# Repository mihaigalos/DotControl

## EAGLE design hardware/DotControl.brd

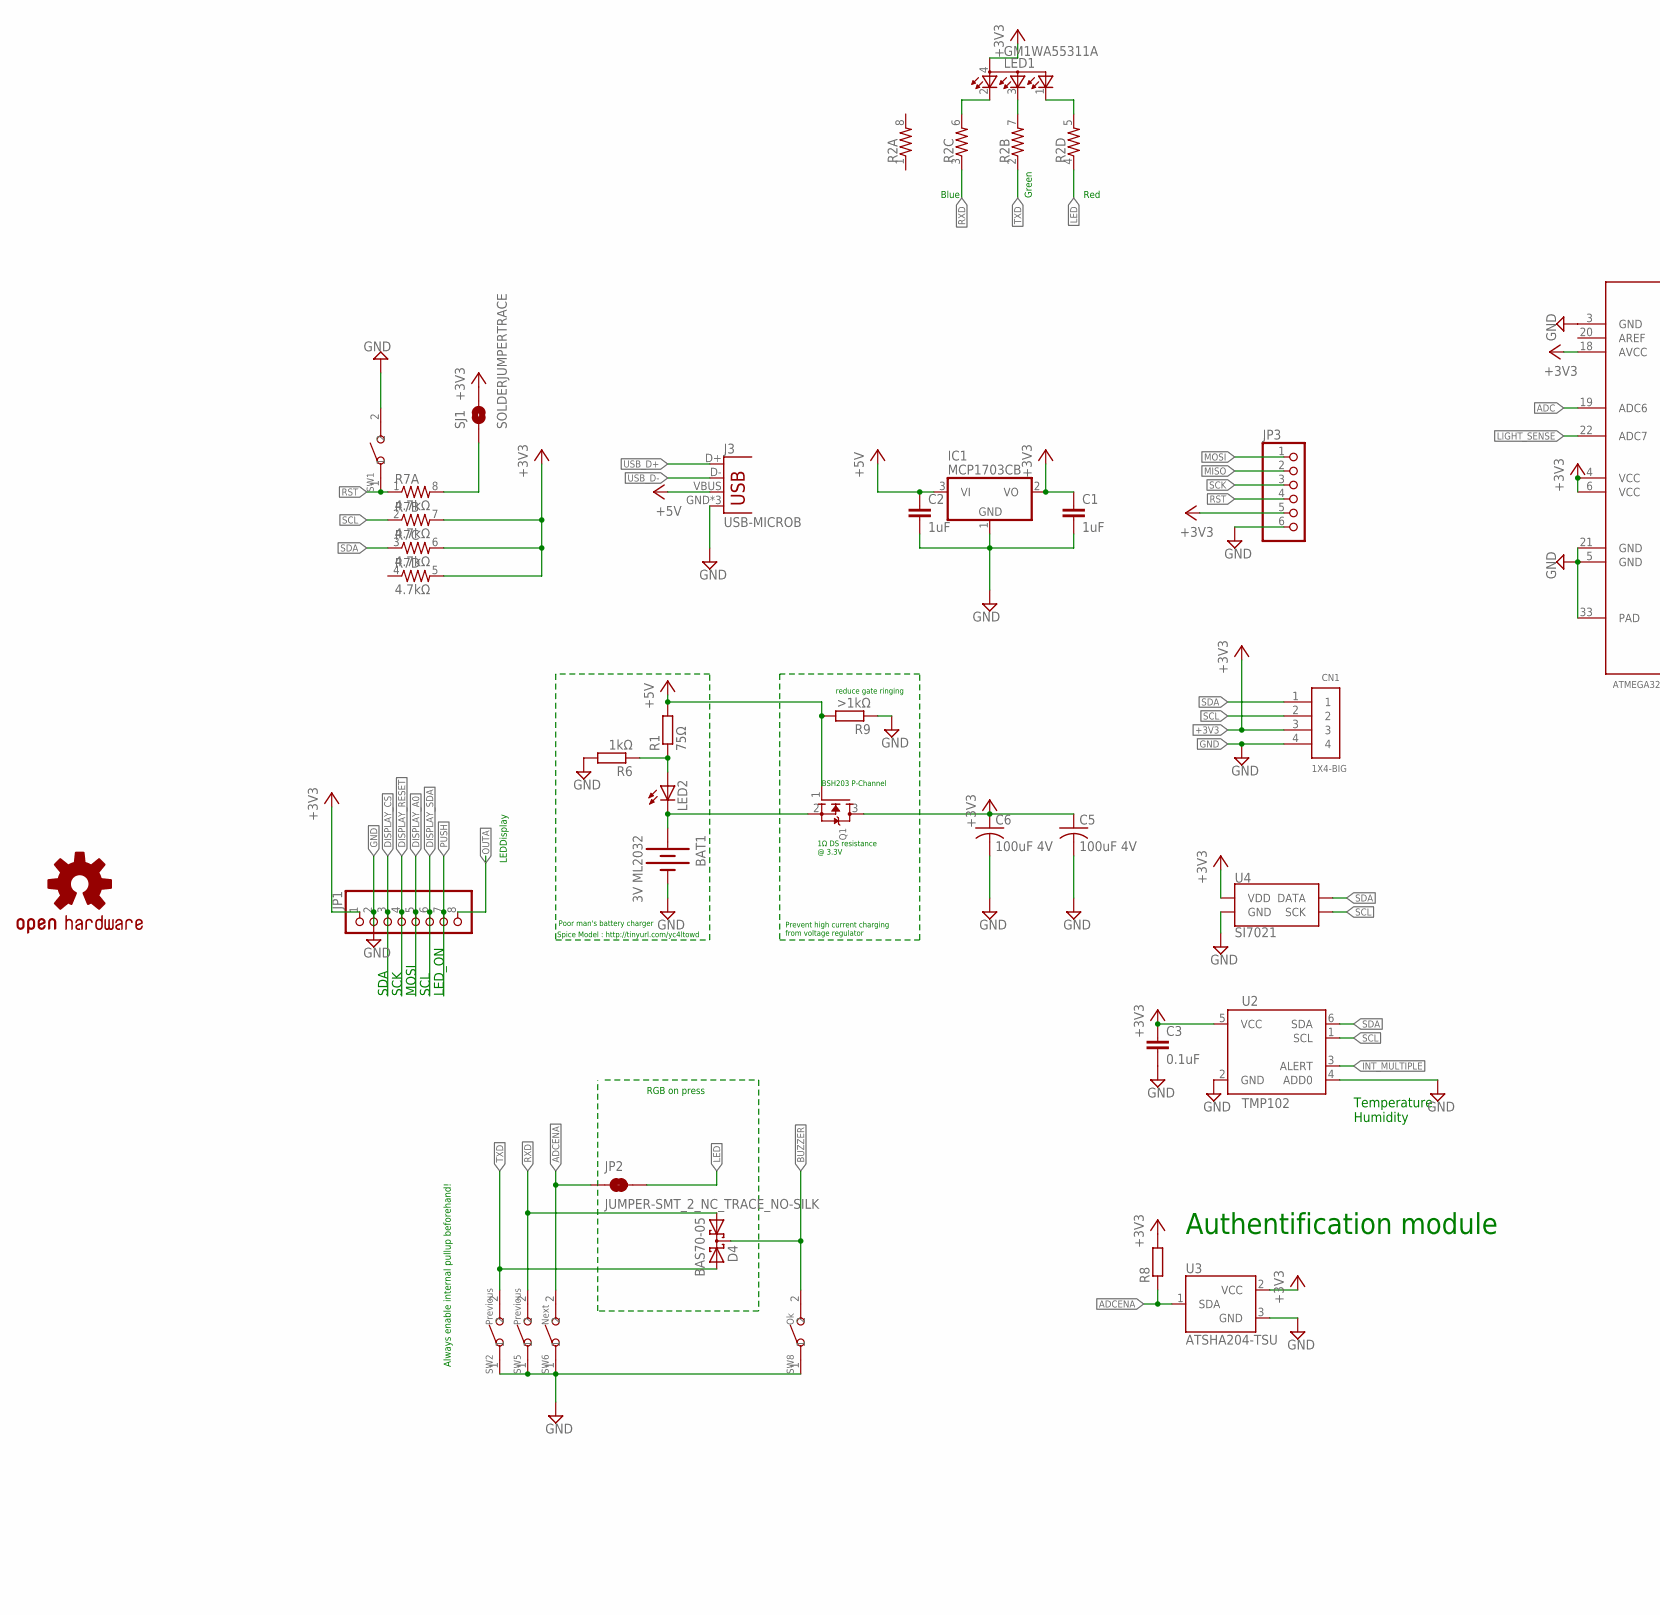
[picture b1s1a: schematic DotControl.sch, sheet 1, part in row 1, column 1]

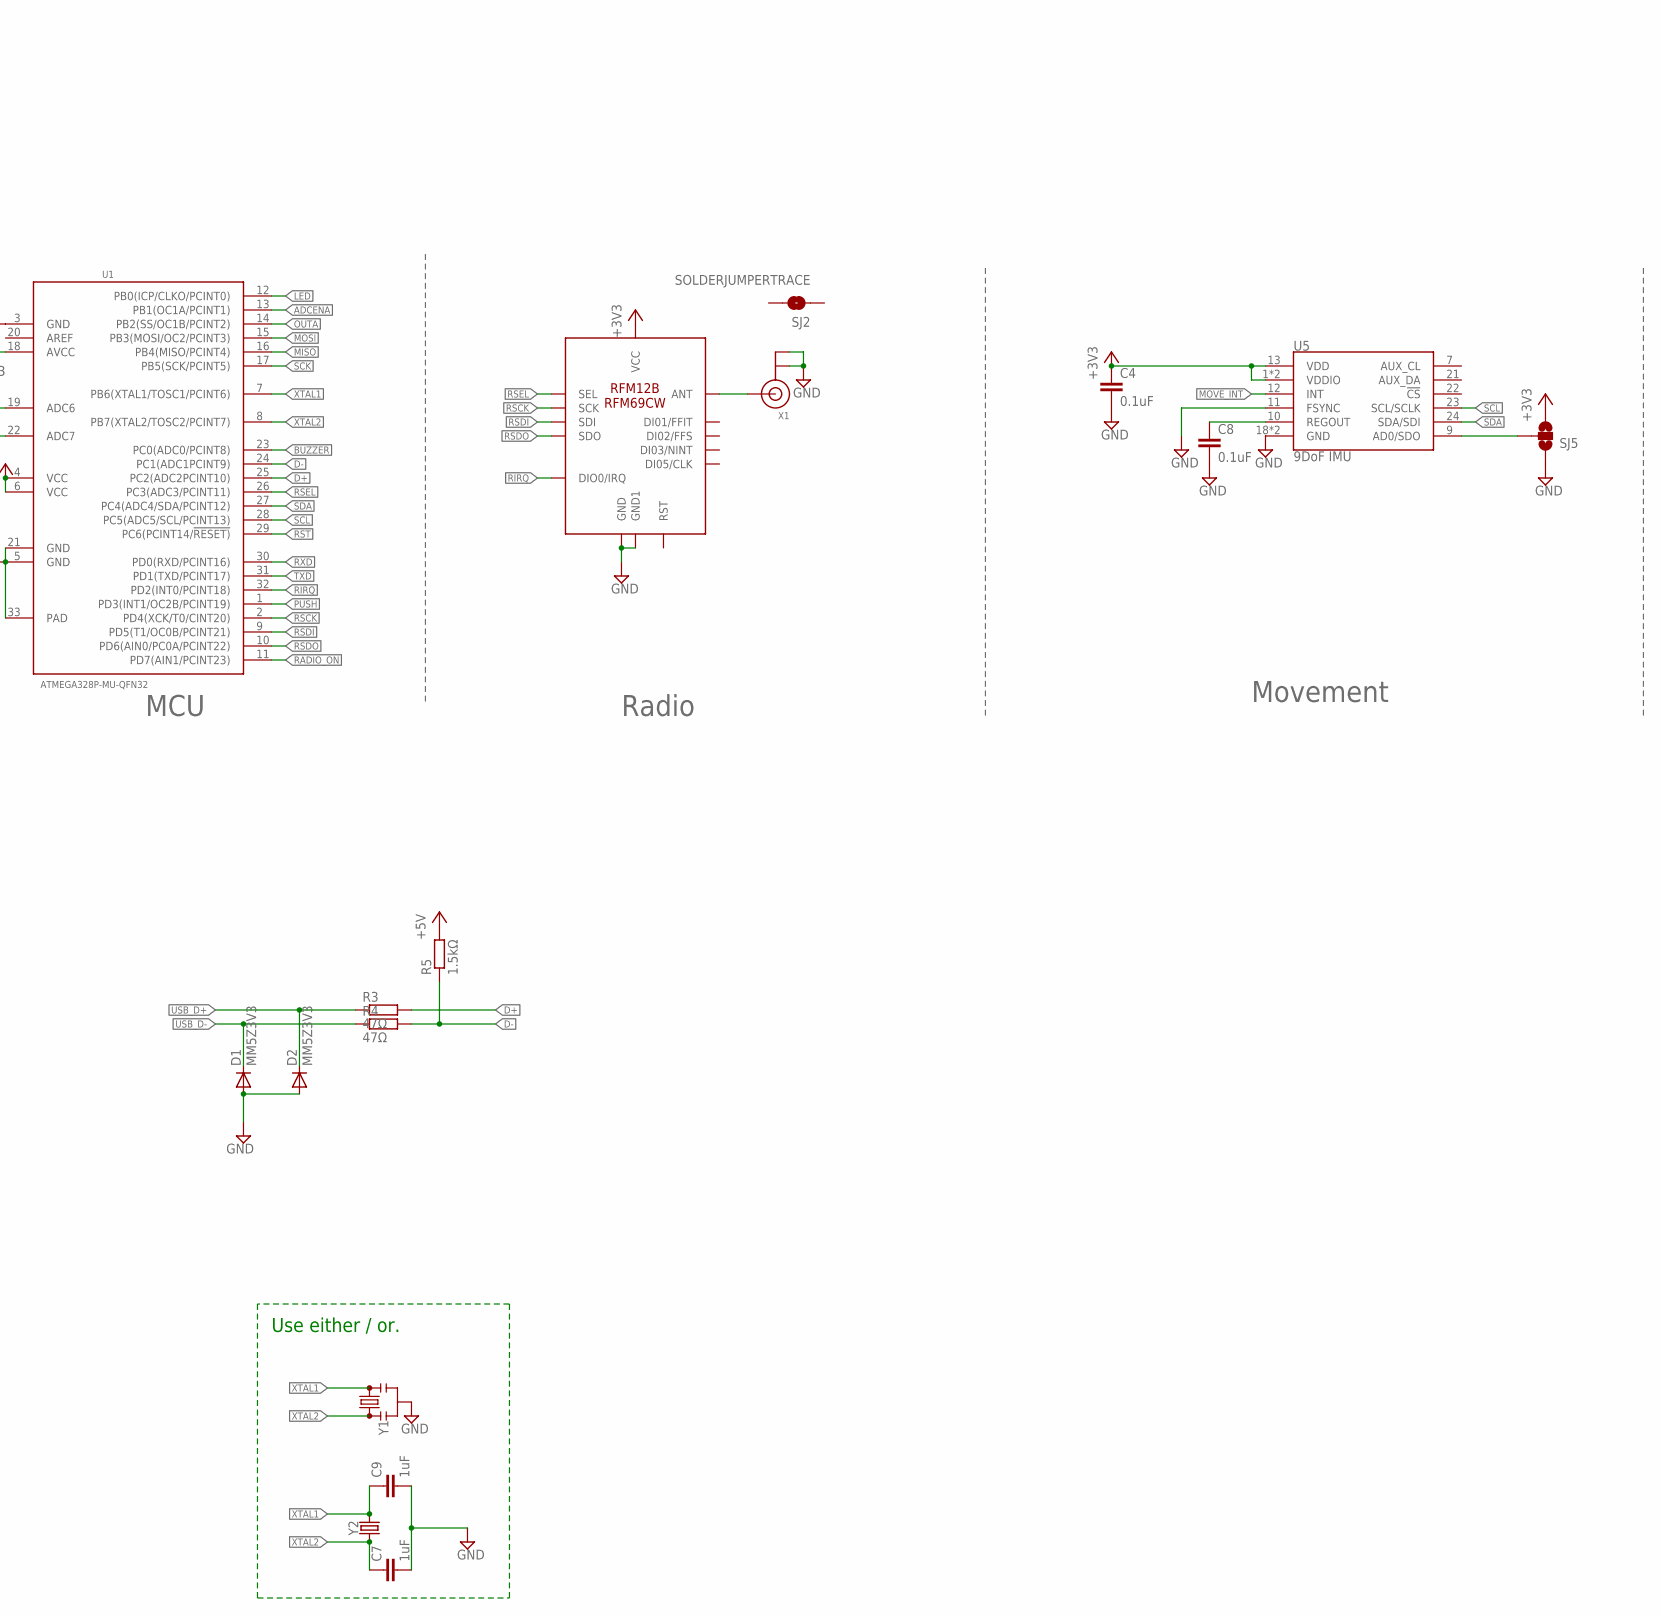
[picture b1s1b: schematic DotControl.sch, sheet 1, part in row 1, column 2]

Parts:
BAT1: 3V ML2032; BATTCOM_20MM_PTH
C1, C2, C7, C9: 1uF; C0603
C3, C4, C8: 0.1uF; C0603
C5, C6: 100uF 4V; C3216
CN1: 1X4-BIG; 1X04-BIG
D1, D2: MM5Z3V3; SOD523
D4: BAS70-05; SOT23
IC1: MCP1703CB; SOT23
J3: USB-MICROB
JP1: PINHD-1X8CLEANBIG; 1X08-CLEANBIG
JP2: JUMPER-SMT_2_NC_TRACE_NO-SILK; SMT-JUMPER_2_NC_TRACE_NO-SILK
JP3: PINHD-1X6; 1X06
LED1: GM1WA55311A
LED2: LED0603; LED-0603
Q1: MOSFET-NREFLOW; SOT23
R1: 75Ω; R0603
R2: RESISTOR-ARRAY0603-ARV; 0603-ARV
R3, R4: 47Ω; R0603
R5: 1.5kΩ; R0603
R6: 1kΩ; R0603
R7: 4.7kΩ; 0603-ARV
R8: R-EU_R0603; R0603
R9: >1kΩ; R0603
SJ1, SJ2: SOLDERJUMPERTRACE; SJ_2S-TRACE
SJ5: SOLDERJUMPER_2WAYS; SJ_3
SW1: SMD-BUTTON(2P-6.0X3.0X2.5MM)-DHT-1163S; SW2-4.0-6.0X3.0X2.5MM
SW2, SW5: Previous; SW2-4.0-6.0X3.0X2.5MM
SW6: Next; SW2-4.0-6.0X3.0X2.5MM
SW8: Ok; SW2-4.0-6.0X3.0X2.5MM
U1: ATMEGA328P-MU-QFN32; QFN32G-0.5-5X5MM
U2: TMP102; SOT563
U3: ATSHA204-TSU; SOT23-3
U4: SI7021; DFN-6-3X3-SI7021
U5: 9DoF IMU; QFN24-3X3
U$1: RFM12B/69CW
U$2: OSHW-LOGOL; OSHW-LOGO-L
X1: ANTENNA_U.FL; U.FL
Y1: RESONATORSMD-3.2X1.3; RESONATOR-SMD-3.2X1.3
Y2: CRYSTALSMD-3.2X1.5; CRYSTAL-SMD-3.2X1.5MM

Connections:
+3V3: C1.1, C3.1, C4.1, C5.1, C6.1, CN1.3, IC1.2 (VO), JP1.1, JP3.5, LED1.4 (A), Q1.3 (D), R7.5 (2), R7.6 (2), R7.7 (2), R8.2, SJ1.2, SJ5.3, U1.4 (VCC), U1.6 (VCC), U1.18 (AVCC), U2.5 (VCC), U3.2 (VCC), U4.VDD, U5.1 (VDDIO), U5.8 (VDDIO), U5.13 (VDD), U$1.VDD (VCC)
+5V: C2.1, IC1.3 (VI), J3.VBUS, Q1.1 (G), R1.2, R5.2, R9.2
ADC: U1.19 (ADC6)
ADCENA: JP2.1, R8.1, SW6.2, U1.13 (PB1(OC1A/PCINT1)), U3.1 (SDA)
BLUE: LED1.2 (CRED), R2.6 (2)
BUZZER: D4.3 (C), SW8.2, U1.23 (PC0(ADC0/PCINT8))
D+: R3.2, U1.25 (PC2(ADC2PCINT10))
D-: R4.2, R5.1, U1.24 (PC1(ADC1PCINT9))
DISPLAY_A0: JP1.5
DISPLAY_CS: JP1.3
DISPLAY_RESET: JP1.4
DISPLAY_SDA: JP1.6
GND: BAT1.2 (-), C1.2, C2.2, C3.2, C4.2, C5.2, C6.2, C7.2, C8.2, C9.2, CN1.4, D1.A, D2.A, IC1.1 (GND), J3.GND, J3.MT1 (GND), J3.MT2 (GND), JP1.2, JP3.6, R6.2, R9.1, SJ5.1, SW1.2, SW2.1, SW5.1, SW6.1, SW8.1, U1.3 (GND), U1.5 (GND), U1.21 (GND), U1.33 (PAD), U2.2 (GND), U2.4 (ADD0), U3.3 (GND), U4.GND, U5.11 (FSYNC), U5.18 (GND), U5.20 (GND), U$1.GND, U$1.GND1, X1.1 (GND), X1.2 (GND), Y1.2
GREEN: LED1.3 (CBLUE), R2.7 (2)
INT_MULTIPLE: U2.3 (ALERT)
LED: JP2.2, R2.4 (1), U1.12 (PB0(ICP/CLKO/PCINT0))
LIGHT_SENSE: U1.22 (ADC7)
MISO: JP3.2, U1.16 (PB4(MISO/PCINT4))
MOSI: JP3.1, U1.15 (PB3(MOSI/OC2/PCINT3))
MOVE_INT: U5.12 (INT)
unnamed: LED2.A, R1.1, R6.1
unnamed: R7.8 (2), SJ1.1
unnamed: U$1.ANT, X1.3 (SIGNAL)
unnamed: SJ5.2, U5.9 (AD0/SDO)
unnamed: C8.1, U5.10 (REGOUT)
unnamed: BAT1.1 (+), LED2.C, Q1.2 (S)
OUTA: JP1.8, U1.14 (PB2(SS/OC1B/PCINT2))
PUSH: JP1.7, U1.1 (PD3(INT1/OC2B/PCINT19))
RADIO_ON: U1.11 (PD7(AIN1/PCINT23))
RED: LED1.1 (CGREEN), R2.5 (2)
RIRQ: U1.32 (PD2(INT0/PCINT18)), U$1.IRQ (DIO0/IRQ)
RSCK: U1.2 (PD4(XCK/T0/CINT20)), U$1.SCK
RSDI: U1.9 (PD5(T1/OC0B/PCINT21)), U$1.SDI
RSDO: U1.10 (PD6(AIN0/PC0A/PCINT22)), U$1.SDO
RSEL: U1.26 (PC3(ADC3/PCINT11)), U$1.SEL
RST: JP3.4, R7.1, SW1.1, U1.29 (PC6(PCINT14/!RESET))
RXD: D4.1 (A1), R2.3 (1), SW5.2, U1.30 (PD0(RXD/PCINT16))
SCK: JP3.3, U1.17 (PB5(SCK/PCINT5))
SCL: CN1.2, R7.2 (1), U1.28 (PC5(ADC5/SCL/PCINT13)), U2.1 (SCL), U4.SCK, U5.23 (SCL/SCLK)
SDA: CN1.1, R7.3 (1), U1.27 (PC4(ADC4/SDA/PCINT12)), U2.6 (SDA), U4.DATA, U5.24 (SDA/SDI)
TXD: D4.2 (A2), R2.2 (1), SW2.2, U1.31 (PD1(TXD/PCINT17))
USB_D+: D2.C, J3.D+, R3.1
USB_D-: D1.C, J3.D-, R4.1
XTAL1: C9.1, U1.7 (PB6(XTAL1/TOSC1/PCINT6)), Y1.3, Y2.P$2 (2)
XTAL2: C7.1, U1.8 (PB7(XTAL2/TOSC2/PCINT7)), Y1.1, Y2.P$1 (1)

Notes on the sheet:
MCU
Radio
Blue
Green
Red
Always enable internal pullup beforehand!
Temperature Humidity
MOSI
SCK
SDA
SCL
LED_ON
LEDDisplay
Authentification module
RGB on press
Movement
Spice Model : http://tinyurl.com/yc4ltowd
BSH203 P-Channel
Poor man's battery charger
Prevent high current charging from voltage regulator
reduce gate ringing
1Ω DS resistance @ 3.3V
Use either / or.

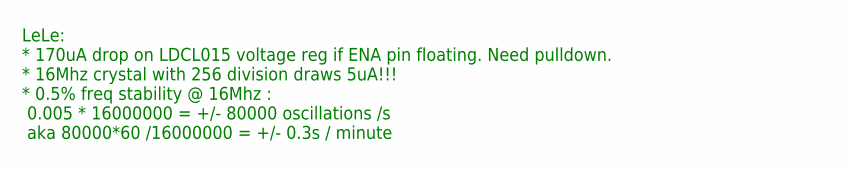
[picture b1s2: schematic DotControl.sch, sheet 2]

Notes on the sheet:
LeLe: * 170uA drop on LDCL015 voltage reg if ENA pin floating. Need pulldown. * 16Mhz crystal with 256 division draws 5uA!!! * 0.5% freq stability @ 16Mhz : 0.005 * 16000000 = +/- 80000 oscillations /s aka 80000*60 /16000000 = +/- 0.3s / minute

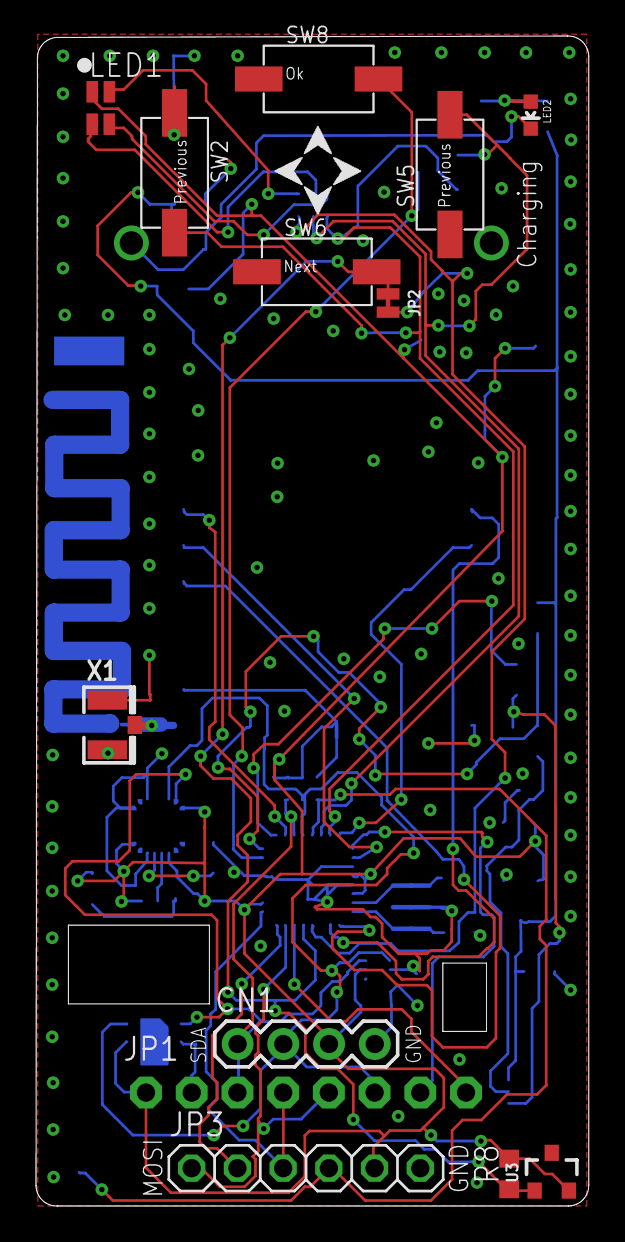
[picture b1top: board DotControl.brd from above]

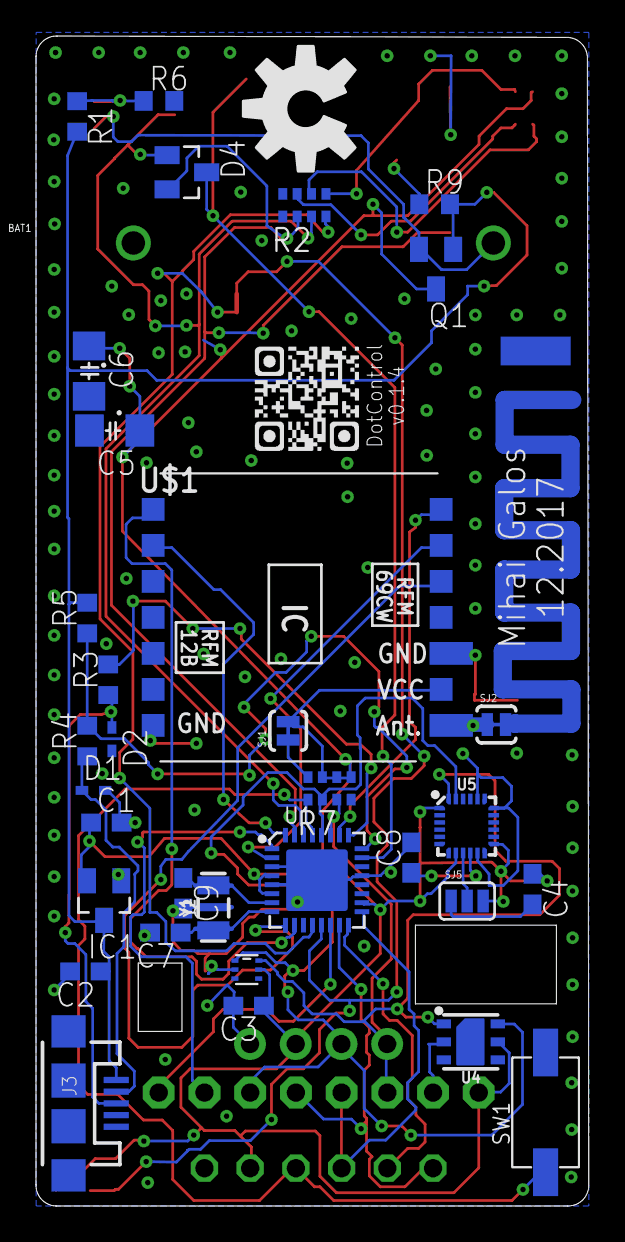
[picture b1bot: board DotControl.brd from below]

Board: 2 copper layers, 30.7 x 65.0 mm, 49 parts (36 on the bottom side), 36 nets.

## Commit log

2017-10-31 Initial version
2017-10-31 Add RGB and crystal
2017-10-31 Add strong GND plane
2017-10-31 Checkpoint
2017-10-31 Add charging led
2017-10-31 Add TMP112 temperature sensor
2017-11-02 Solidify GND plane
2017-11-02 Add connections for 128x128
2017-11-02 Add hardware/ and .gitignore
2017-11-02 Update ignore rules
2017-11-02 Add QR and timestamp
2017-11-03 Update QR rotation
2017-11-03 Update display supply to 3.3V, charging of battery
2017-11-03 Rotate temp sensor
2017-11-03 Minor rearrange wires
2017-11-03 Improve routing and vias
2017-11-03 Add rounded corners
2017-11-05 Amend
2017-11-05 Add CryptoAuthentication module
2017-11-05 Reposition crypto module
2017-11-18 Add key to RGB
2017-11-18 Add PCB antenna
2017-11-18 Increase clearance of antenna
2017-11-18 Add missing 3V3 connection to battery
2017-11-18 Improve GND
2017-11-18 Edit ToDos
2017-11-19 Add HW support for USB bootloading
2017-11-19 Reassign push buttons
2017-11-19 Setting vias near rgb R-array further apart
2017-11-19 Swap R with B @ pushbutton
2017-11-19 Light RGB composite colors on push press
2017-11-19 Add Si7021 temp sensor
2017-11-19 Add I2C text
2017-11-20 [Beta] Add HW support for MPU9250
2017-11-22 Add caps for MPU9250, V divider for battery charge
2017-11-22 Tidy up logos of Rs
2017-11-22 Readjust R values for charger, add Spice link
2017-11-25 Add pulldown on ENA pin of voltage reg to prefent 150uA quiescent current
2017-11-25 Add pulldown on ENA pin of voltage reg to prevent 150uA quiescent current
2017-11-25 [Intermediate] Improve coincell charging
2017-11-26 Replace LDO with low quiescence regulator
2017-11-26 Clean warnings
2017-11-26 Improve GND, increase version
2017-11-26 2x100uF instead of 1x1000uF
2017-11-26 Add .gitattributes for eagle-diff
2017-11-26 Update LeLe: 16Mhz with 256 divider = 5uA draw
2017-11-26 Update LeLe: +/-0.3s / minute drift @ 16Mhz
2017-11-30 Add support for 10ppm crystal
2017-12-06 Add missing pullup to crypto chip
2017-12-17 Fix info text: BSH103 is N-Channel
2017-12-17 Replace BSH103 with BSH203 for charging battery
2017-12-18 Fix MOSFET bridge of G-D

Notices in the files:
parts and their libraries:
SparkFun: Licensing: CC v3.0 Share-Alike You are welcome to use this library for commercial purposes.
SparkFun-Retired: Licensing: Creative Commons ShareAlike 4.0 International - https://creativecommons.org/licenses/by-sa/4.0
